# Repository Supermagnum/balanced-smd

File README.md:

# balanced-smd
A small PCB that uses two LT6234CS8#TRPBF  op amps to amplify a signal from a contact microphone.

It has balanced output,input and should run on +48 phantom power. Shielded cable must with 3 leads be used for connection to the piezo crystals. Please use 0,5 W metal film resistors with 1% tolerance or better and audio quality capacitors.
C0G (NP0) or X7R capacitors is very good.

It is important that the circuit board is mounted inside a metal box, and Ø2mm conducting metal standoffs are used. The corner pads of the PCB board is reserved for that. Of course the PCB board and components must not come in contact with any metal surface expect the standoffs.

The circuit may benefit from a Zobel network, that is a 680 pF capacitor and a 150 ohms resistor in series between pin 2 and 3 on the output or the input connector. It should avoid high frequency oscillation in the cable.

Schematic diagram:
https://github.com/Supermagnum/balanced-smd/blob/main/smd-balanced.pdf

Component side picture with switch settings versus gain in dB:
https://github.com/Supermagnum/balanced-smd/blob/main/front.jpg

Back side:
https://github.com/Supermagnum/balanced-smd/blob/main/back.jpg

Aisler link:
https://aisler.net/p/YIWINLSK
Aisler can suply this assembled with the SMD components in place.

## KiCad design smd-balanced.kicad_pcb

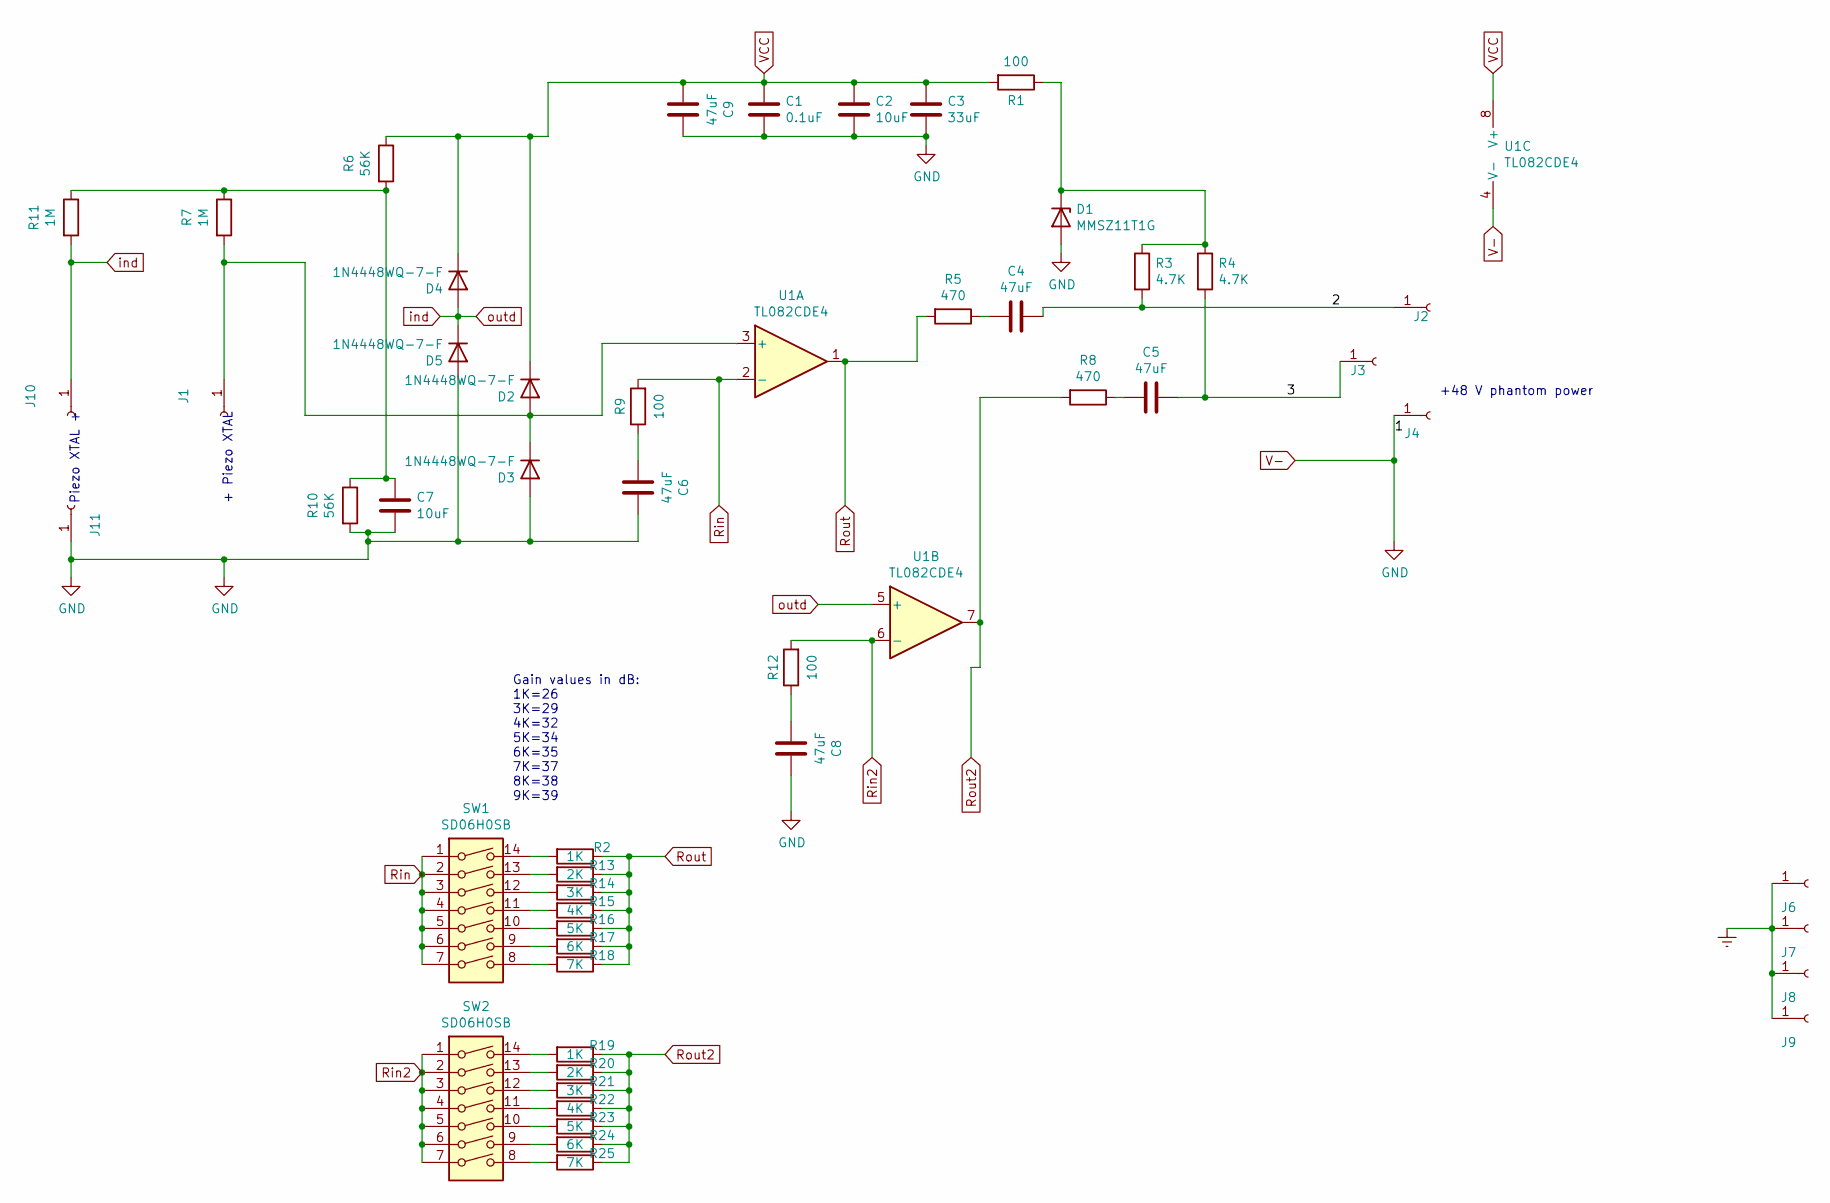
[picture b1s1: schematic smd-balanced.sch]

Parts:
C1: 0.1uF; C_0201_0603Metric_Pad0.64x0.40mm_HandSolder
C2, C7: 10uF; C_0201_0603Metric_Pad0.64x0.40mm_HandSolder
C3: 33uF; C_0201_0603Metric_Pad0.64x0.40mm_HandSolder
C4, C5, C6, C8, C9: 47uF; C_0201_0603Metric_Pad0.64x0.40mm_HandSolder
D1: MMSZ11T1G; D_SOD-123
D2, D3, D4, D5: 1N4448WQ-7-F; D_SOD-123
J1, J2, J3, J4, J6, J7, J8, J9, J10, J11: Conn_01x01_Female; MountingHole_2.2mm_M2_ISO7380_Pad
R1, R9, R12: 100; R_0603_1608Metric
R2, R19: 1K; R_0603_1608Metric
R3, R4: 4.7K; R_0603_1608Metric
R5, R8: 470; R_0603_1608Metric
R6, R10: 56K; R_0603_1608Metric
R7, R11: 1M; R_0603_1608Metric
R13, R20: 2K; R_0603_1608Metric
R14, R21: 3K; R_0603_1608Metric
R15, R22: 4K; R_0603_1608Metric
R16, R23: 5K; R_0603_1608Metric
R17, R24: 6K; R_0805_2012Metric
R18, R25: 7K; R_0805_2012Metric
SW1, SW2: SD06H0SB; SD07H1SB
U1: TL082CDE4; SOIC-8_3.9x4.9mm_P1.27mm

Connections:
/2: C4.1, J2.1, R3.2
/3: C5.1, J3.1, R4.2
Earth: J6.1, J7.1, J8.1, J9.1
unnamed: C4.2, R5.1
unnamed: C5.2, R8.1
unnamed: C6.2, R9.1
unnamed: C7.1, R6.2, R7.1, R10.1, R11.1
unnamed: C8.2, R12.1
unnamed: D1.1 (K), R1.1, R3.1, R4.1
unnamed: D2.2 (A), D3.1 (K), J1.1, R7.2, U1.3 (+)
unnamed: R2.2, SW1.14
unnamed: R13.2, SW1.13
unnamed: R14.2, SW1.12
unnamed: R15.2, SW1.11
unnamed: R16.2, SW1.10
unnamed: R17.2, SW1.9
unnamed: R18.2, SW1.8
unnamed: R19.2, SW2.14
unnamed: R20.2, SW2.13
unnamed: R21.2, SW2.12
unnamed: R22.2, SW2.11
unnamed: R23.2, SW2.10
unnamed: R24.2, SW2.9
unnamed: R25.2, SW2.8
Rin: R9.2, SW1.1, SW1.2, SW1.3, SW1.4, SW1.5, SW1.6, SW1.7, U1.2 (-)
Rin2: R12.2, SW2.1, SW2.2, SW2.3, SW2.4, SW2.5, SW2.6, SW2.7, U1.6 (-)
Rout: R2.1, R5.2, R13.1, R14.1, R15.1, R16.1, R17.1, R18.1, U1.1
Rout2: R8.2, R19.1, R20.1, R21.1, R22.1, R23.1, R24.1, R25.1, U1.7
V-: C1.2, C2.2, C3.2, C6.1, C7.2, C8.1, C9.1, D1.2 (A), D3.2 (A), D5.2 (A), J4.1, J11.1, R10.2, U1.4 (V-)
VCC: C1.1, C2.1, C3.1, C9.2, D2.1 (K), D4.1 (K), R1.2, R6.1, U1.8 (V+)
ind: D4.2 (A), D5.1 (K), J10.1, R11.2, U1.5 (+)

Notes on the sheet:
+48 V phantom power
Gain values in dB: 1K=26 3K=29 4K=32 5K=34 6K=35 7K=37 8K=38 9K=39
+ Piezo XTAL
Piezo XTAL +

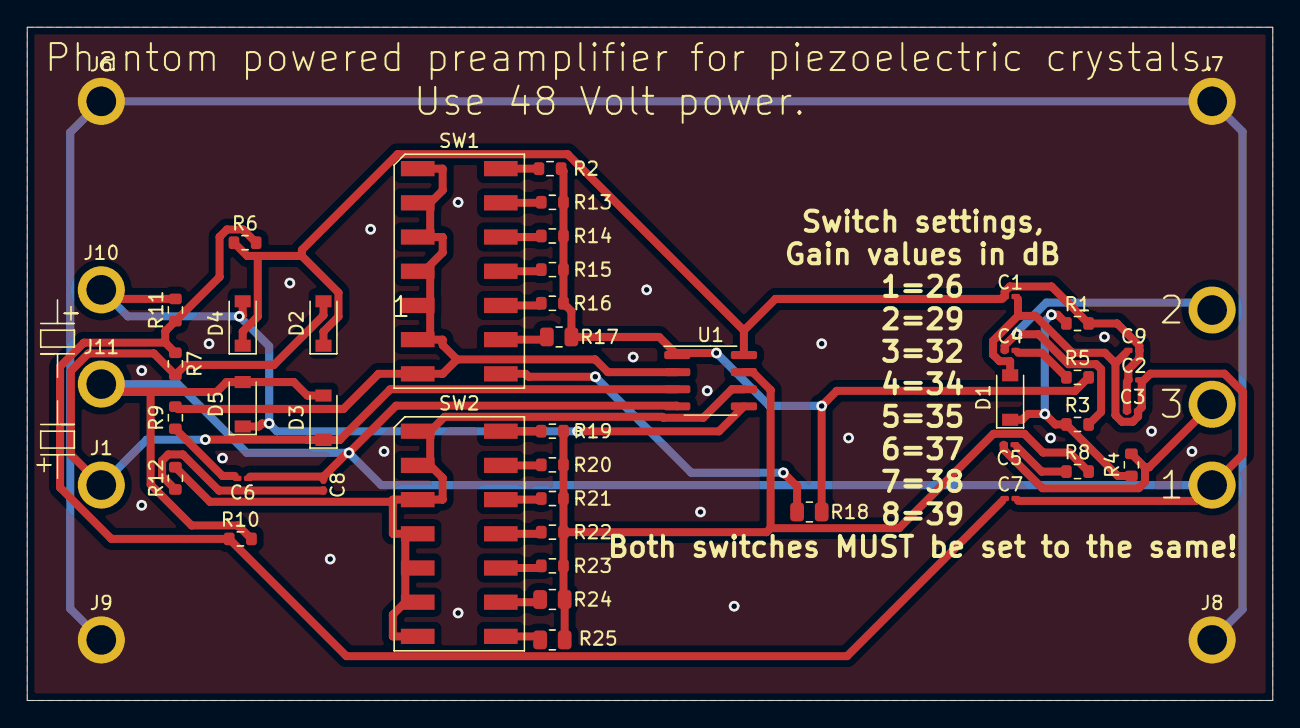
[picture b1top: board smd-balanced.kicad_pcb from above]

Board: 2 copper layers, 92.5 x 50.0 mm, 52 parts (0 on the bottom side), 31 nets.

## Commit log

2021-07-17 Update README.md
    changed to TL082CDE4 opamps
